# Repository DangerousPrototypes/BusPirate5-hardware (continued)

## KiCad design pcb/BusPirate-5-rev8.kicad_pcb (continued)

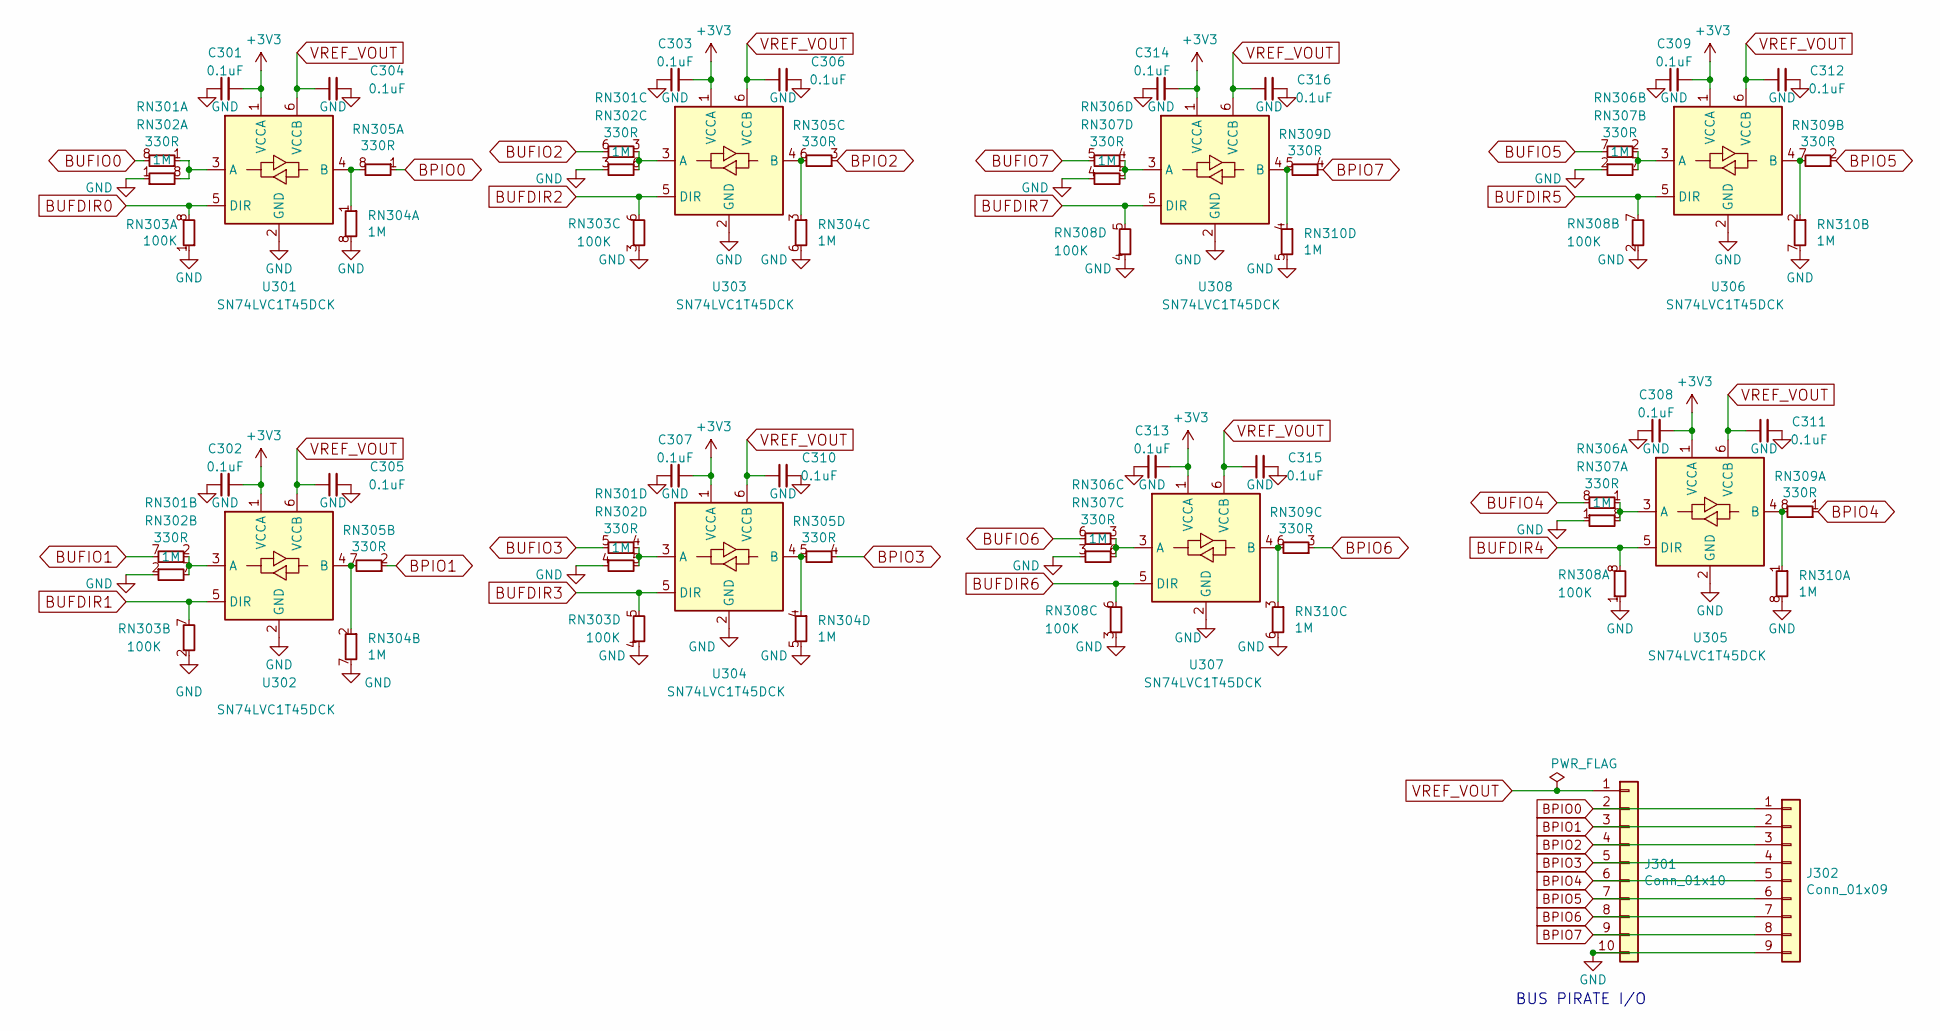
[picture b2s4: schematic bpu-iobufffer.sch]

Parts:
C301, C302, C303, C304, C305, C306, C307, C308, C309, C310, C311, C312, C313, C314, C315, C316: 0.1uF; C_0402_1005Metric
J301: Conn_01x10; PinHeader_1x10_P2.54mm_Vertical
J302: Conn_01x09; JST_SH_SM09B-SRSS-TB_1x09-1MP_P1.00mm_Horizontal
RN301, RN305, RN306, RN309: 330R; R_Array_Convex_4x0402
RN302, RN304, RN307, RN310: 1M; R_Array_Convex_4x0402
RN303, RN308: 100K; R_Array_Convex_4x0402
U301, U302, U303, U304, U305, U306, U307, U308: SN74LVC1T45DCK; SOT-363_SC-70-6

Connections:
BPIO0: J301.2, J302.1, RN305.1 (R1.1); also elsewhere on the board
BPIO1: J301.3, J302.2, RN305.2 (R1.1); also elsewhere on the board
BPIO2: J301.4, J302.3, RN305.3 (R1.1); also elsewhere on the board
BPIO3: J301.5, J302.4, RN305.4 (R1.1); also elsewhere on the board
BPIO4: J301.6, J302.5, RN309.1 (R1.1); also elsewhere on the board
BPIO5: J301.7, J302.6, RN309.2 (R1.1); also elsewhere on the board
BPIO6: J301.8, J302.7, RN309.3 (R1.1); also elsewhere on the board
BPIO7: J301.9, J302.8, RN309.4 (R1.1); also elsewhere on the board
BUFDIR0: RN303.8 (R1.8), U301.5 (DIR); also elsewhere on the board
BUFDIR1: RN303.7 (R1.8), U302.5 (DIR); also elsewhere on the board
BUFDIR2: RN303.6 (R1.8), U303.5 (DIR); also elsewhere on the board
BUFDIR3: RN303.5 (R1.8), U304.5 (DIR); also elsewhere on the board
BUFDIR4: RN308.8 (R1.8), U305.5 (DIR); also elsewhere on the board
BUFDIR5: RN308.7 (R1.8), U306.5 (DIR); also elsewhere on the board
BUFDIR6: RN308.6 (R1.8), U307.5 (DIR); also elsewhere on the board
BUFDIR7: RN308.5 (R1.8), U308.5 (DIR); also elsewhere on the board
BUFIO0: RN301.8 (R1.8); also elsewhere on the board
BUFIO1: RN301.7 (R1.8); also elsewhere on the board
BUFIO2: RN301.6 (R1.8); also elsewhere on the board
BUFIO3: RN301.5 (R1.8); also elsewhere on the board
BUFIO4: RN306.8 (R1.8); also elsewhere on the board
BUFIO5: RN306.7 (R1.8); also elsewhere on the board
BUFIO6: RN306.6 (R1.8); also elsewhere on the board
BUFIO7: RN306.5 (R1.8); also elsewhere on the board
GND: C301.1, C302.1, C303.1, C304.2, C305.2, C306.2, C307.1, C308.1, C309.1, C310.2, C311.2, C312.2, C313.1, C314.1, C315.2, C316.2, J301.10, J302.9, RN302.1 (R1.1), RN302.2 (R1.1), RN302.3 (R1.1), RN302.4 (R1.1), RN303.1 (R1.1), RN303.2 (R1.1), RN303.3 (R1.1), RN303.4 (R1.1), RN304.5 (R1.8), RN304.6 (R1.8), RN304.7 (R1.8), RN304.8 (R1.8), RN307.1 (R1.1), RN307.2 (R1.1), RN307.3 (R1.1), RN307.4 (R1.1), RN308.1 (R1.1), RN308.2 (R1.1), RN308.3 (R1.1), RN308.4 (R1.1), RN310.5 (R1.8), RN310.6 (R1.8), RN310.7 (R1.8), RN310.8 (R1.8), U301.2 (GND), U302.2 (GND), U303.2 (GND), U304.2 (GND), U305.2 (GND), U306.2 (GND), U307.2 (GND), U308.2 (GND); also elsewhere on the board
unnamed: RN301.1 (R1.1), RN302.8 (R1.8), U301.3 (A)
unnamed: RN301.2 (R1.1), RN302.7 (R1.8), U302.3 (A)
unnamed: RN301.3 (R1.1), RN302.6 (R1.8), U303.3 (A)
unnamed: RN301.4 (R1.1), RN302.5 (R1.8), U304.3 (A)
unnamed: RN304.1 (R1.1), RN305.8 (R1.8), U301.4 (B)
unnamed: RN304.2 (R1.1), RN305.7 (R1.8), U302.4 (B)
unnamed: RN304.3 (R1.1), RN305.6 (R1.8), U303.4 (B)
unnamed: RN304.4 (R1.1), RN305.5 (R1.8), U304.4 (B)
unnamed: RN306.1 (R1.1), RN307.8 (R1.8), U305.3 (A)
unnamed: RN306.2 (R1.1), RN307.7 (R1.8), U306.3 (A)
unnamed: RN306.3 (R1.1), RN307.6 (R1.8), U307.3 (A)
unnamed: RN306.4 (R1.1), RN307.5 (R1.8), U308.3 (A)
unnamed: RN309.5 (R1.8), RN310.4 (R1.1), U308.4 (B)
unnamed: RN309.6 (R1.8), RN310.3 (R1.1), U307.4 (B)
unnamed: RN309.7 (R1.8), RN310.2 (R1.1), U306.4 (B)
unnamed: RN309.8 (R1.8), RN310.1 (R1.1), U305.4 (B)
VREF_VOUT: C304.1, C305.1, C306.1, C310.1, C311.1, C312.1, C315.1, C316.1, J301.1, U301.6 (VCCB), U302.6 (VCCB), U303.6 (VCCB), U304.6 (VCCB), U305.6 (VCCB), U306.6 (VCCB), U307.6 (VCCB), U308.6 (VCCB); also elsewhere on the board

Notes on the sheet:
BUS PIRATE I/O

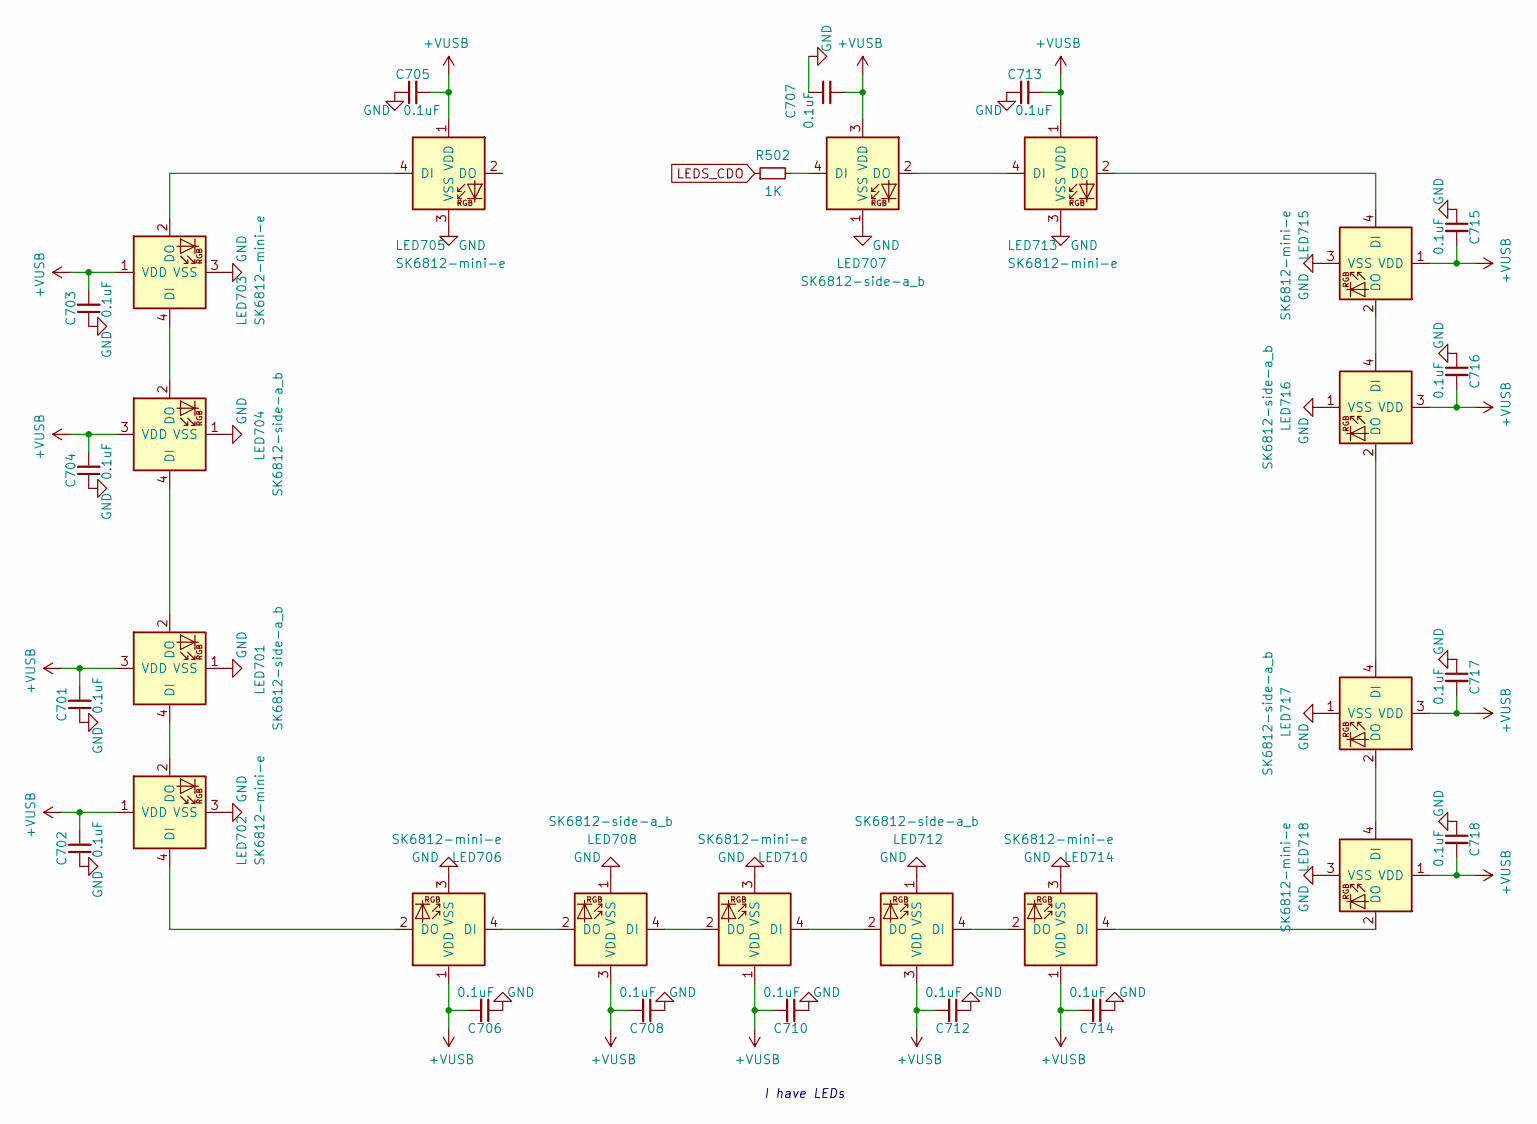
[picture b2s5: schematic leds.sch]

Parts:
C701, C702, C703, C704, C705, C706, C707, C708, C710, C712, C713, C714, C715, C716, C717, C718: 0.1uF; C_0402_1005Metric
LED701, LED704, LED707, LED708, LED712, LED716, LED717: SK6812-side-a_b
LED702, LED703, LED705, LED706, LED710, LED713, LED714, LED715, LED718: SK6812-mini-e
R502: 1K; R_0402_1005Metric

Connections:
+VUSB: C701.2, C702.2, C703.2, C704.2, C705.2, C706.2, C707.2, C708.2, C710.2, C712.2, C713.2, C714.2, C715.2, C716.2, C717.2, C718.2, LED701.3 (VDD), LED702.1 (VDD), LED703.1 (VDD), LED704.3 (VDD), LED705.1 (VDD), LED706.1 (VDD), LED707.3 (VDD), LED708.3 (VDD), LED710.1 (VDD), LED712.3 (VDD), LED713.1 (VDD), LED714.1 (VDD), LED715.1 (VDD), LED716.3 (VDD), LED717.3 (VDD), LED718.1 (VDD); also elsewhere on the board
GND: C701.1, C702.1, C703.1, C704.1, C705.1, C706.1, C707.1, C708.1, C710.1, C712.1, C713.1, C714.1, C715.1, C716.1, C717.1, C718.1, LED701.1 (VSS), LED702.3 (VSS), LED703.3 (VSS), LED704.1 (VSS), LED705.3 (VSS), LED706.3 (VSS), LED707.1 (VSS), LED708.1 (VSS), LED710.3 (VSS), LED712.1 (VSS), LED713.3 (VSS), LED714.3 (VSS), LED715.3 (VSS), LED716.1 (VSS), LED717.1 (VSS), LED718.3 (VSS); also elsewhere on the board
LEDS_CDO: R502.1; also elsewhere on the board
unnamed: LED701.2 (DO), LED704.4 (DI)
unnamed: LED701.4 (DI), LED702.2 (DO)
unnamed: LED702.4 (DI), LED706.2 (DO)
unnamed: LED703.2 (DO), LED705.4 (DI)
unnamed: LED703.4 (DI), LED704.2 (DO)
unnamed: LED706.4 (DI), LED708.2 (DO)
unnamed: LED707.2 (DO), LED713.4 (DI)
unnamed: LED707.4 (DI), R502.2
unnamed: LED708.4 (DI), LED710.2 (DO)
unnamed: LED710.4 (DI), LED712.2 (DO)
unnamed: LED712.4 (DI), LED714.2 (DO)
unnamed: LED713.2 (DO), LED715.4 (DI)
unnamed: LED714.4 (DI), LED718.2 (DO)
unnamed: LED715.2 (DO), LED716.4 (DI)
unnamed: LED716.2 (DO), LED717.4 (DI)
unnamed: LED717.2 (DO), LED718.4 (DI)

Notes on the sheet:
I have LEDs

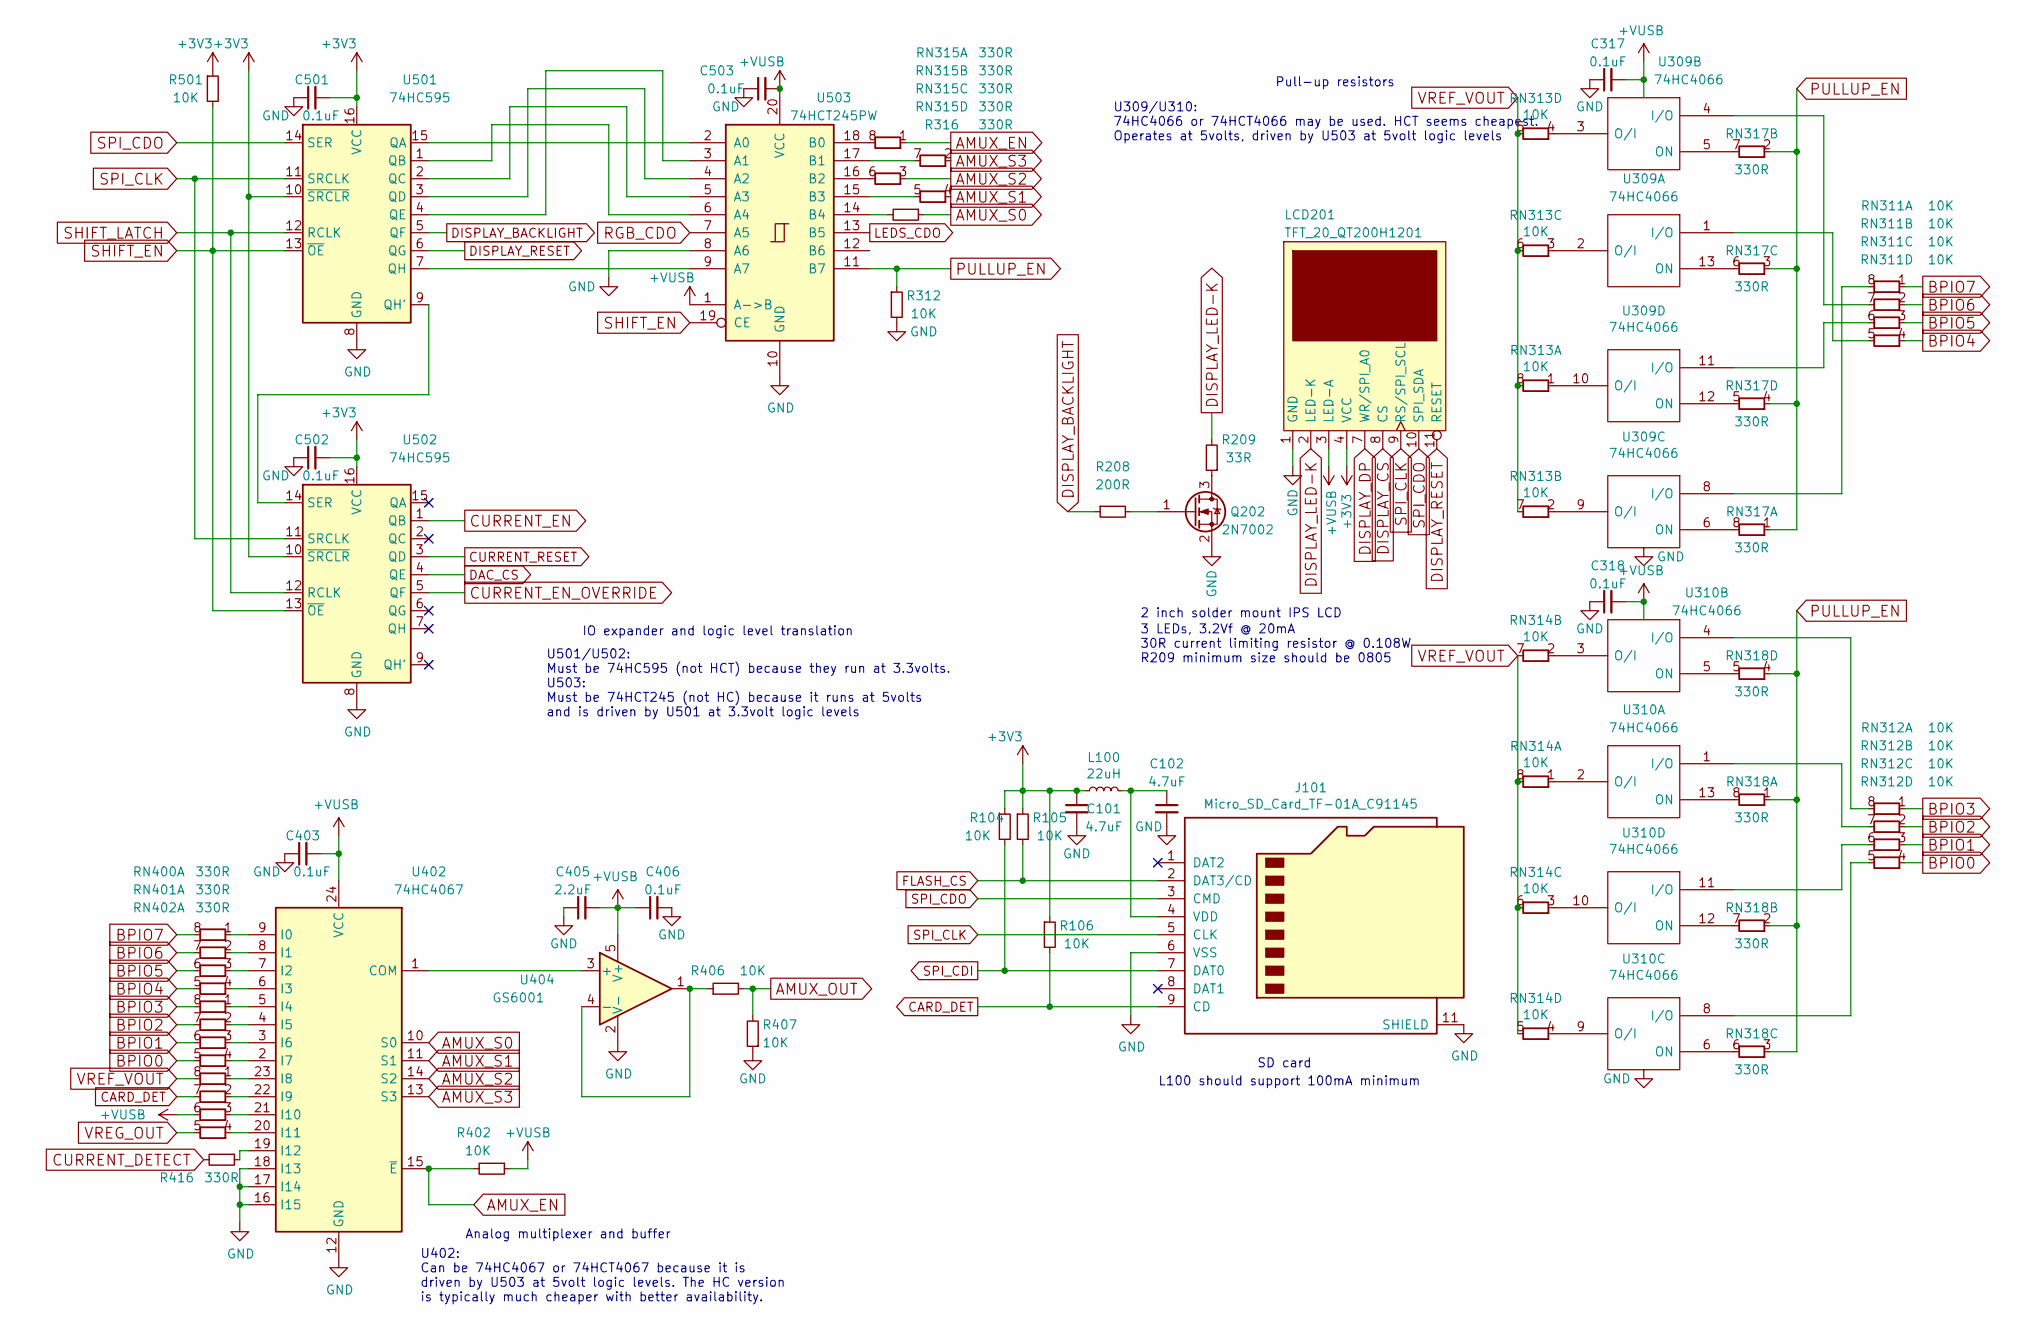
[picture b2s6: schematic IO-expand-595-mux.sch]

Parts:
C101, C102: 4.7uF; C_0402_1005Metric
C317, C318, C403, C406, C501, C502, C503: 0.1uF; C_0402_1005Metric
C405: 2.2uF; C_0402_1005Metric
J101: Micro_SD_Card_TF-01A_C91145; TF-01A_C91145
L100: 22uH; L_0603_1608Metric
LCD201: TFT_20_QT200H1201
Q202: 2N7002; SOT-23
R104, R105, R106, R312, R402, R406, R407, R501: 10K; R_0402_1005Metric
R208: 200R; R_0402_1005Metric
R209: 33R; R_0805_2012Metric
R316, R416: 330R; R_0402_1005Metric
RN311, RN312, RN313, RN314: 10K; R_Array_Convex_4x0402
RN315, RN317, RN318, RN400, RN401, RN402: 330R; R_Array_Convex_4x0402
U309, U310: 74HC4066; TSSOP-14_4.4x5mm_P0.65mm
U402: 74HC4067; TSSOP-24_4.4x7.8mm_P0.65mm
U404: GS6001; SOT-23-5
U501, U502: 74HC595; TSSOP-16_4.4x5mm_P0.65mm
U503: 74HCT245PW; TSSOP-20_4.4x6.5mm_P0.65mm

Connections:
+VUSB: C317.2, C318.2, C403.2, C405.2, C406.1, C503.2, LCD201.3 (LED-A), R402.1, RN402.6 (R1.8), U309.14 (Vdd), U310.14 (Vdd), U402.24 (VCC), U404.5 (V+), U503.1 (A->B), U503.20 (VCC); also elsewhere on the board
AMUX_EN: R402.2, RN315.1 (R1.1), U402.15 (~E)
AMUX_OUT: R406.2, R407.2; also elsewhere on the board
AMUX_S0: R316.1, U402.10 (S0)
AMUX_S1: RN315.4 (R1.1), U402.11 (S1)
AMUX_S2: RN315.3 (R1.1), U402.14 (S2)
AMUX_S3: RN315.2 (R1.1), U402.13 (S3)
BPIO0: RN312.4 (R1.1), RN401.5 (R1.8); also elsewhere on the board
BPIO1: RN312.3 (R1.1), RN401.6 (R1.8); also elsewhere on the board
BPIO2: RN312.2 (R1.1), RN401.7 (R1.8); also elsewhere on the board
BPIO3: RN312.1 (R1.1), RN401.8 (R1.8); also elsewhere on the board
BPIO4: RN311.4 (R1.1), RN400.5 (R1.8); also elsewhere on the board
BPIO5: RN311.3 (R1.1), RN400.6 (R1.8); also elsewhere on the board
BPIO6: RN311.2 (R1.1), RN400.7 (R1.8); also elsewhere on the board
BPIO7: RN311.1 (R1.1), RN400.8 (R1.8); also elsewhere on the board
CARD_DET: J101.9 (CD), R106.2, RN402.7 (R1.8)
CURRENT_DETECT: R416.2; also elsewhere on the board
CURRENT_EN: U502.1 (QB); also elsewhere on the board
CURRENT_EN_OVERRIDE: U502.5 (QF); also elsewhere on the board
CURRENT_RESET: U502.3 (QD); also elsewhere on the board
DAC_CS: U502.4 (QE)
DISPLAY_BACKLIGHT: R208.1, U501.5 (QF)
DISPLAY_CS: LCD201.8 (CS); also elsewhere on the board
DISPLAY_DP: LCD201.7 (WR/SPI_A0); also elsewhere on the board
DISPLAY_LED-K: LCD201.2 (LED-K), R209.2
DISPLAY_RESET: LCD201.11 (RESET), U501.6 (QG)
FLASH_CS: J101.2 (DAT3/CD), R105.2; also elsewhere on the board
GND: C101.2, C102.2, C317.1, C318.1, C403.1, C405.1, C406.2, C501.1, C502.1, C503.1, J101.6 (VSS), J101.11 (SHIELD), LCD201.1 (GND), LCD201.5 (GND), LCD201.6 (GND), LCD201.12 (GND), Q202.2 (S), R312.2, R407.1, U309.7 (Vss), U310.7 (Vss), U402.12 (GND), U402.16 (I15), U402.17 (I14), U402.18 (I13), U404.2 (V-), U501.8 (GND), U502.8 (GND), U503.8 (A6), U503.10 (GND); also elsewhere on the board
LEDS_CDO: U503.13 (B5); also elsewhere on the board
unnamed: C102.1, J101.4 (VDD), L100.2
unnamed: Q202.1 (G), R208.2
unnamed: Q202.3 (D), R209.1
unnamed: R316.2, U503.14 (B4)
unnamed: R406.1, U404.1, U404.4 (-)
unnamed: R416.1, U402.19 (I12)
unnamed: RN311.5 (R1.8), U309.1 (I/O)
unnamed: RN311.6 (R1.8), U309.11 (I/O)
unnamed: RN311.7 (R1.8), U309.4 (I/O)
unnamed: RN311.8 (R1.8), U309.8 (I/O)
unnamed: RN312.5 (R1.8), U310.8 (I/O)
unnamed: RN312.6 (R1.8), U310.11 (I/O)
unnamed: RN312.7 (R1.8), U310.1 (I/O)
unnamed: RN312.8 (R1.8), U310.4 (I/O)
unnamed: RN313.1 (R1.1), U309.10 (O/I)
unnamed: RN313.2 (R1.1), U309.9 (O/I)
unnamed: RN313.3 (R1.1), U309.2 (O/I)
unnamed: RN313.4 (R1.1), U309.3 (O/I)
unnamed: RN314.1 (R1.1), U310.2 (O/I)
unnamed: RN314.2 (R1.1), U310.3 (O/I)
unnamed: RN314.3 (R1.1), U310.10 (O/I)
unnamed: RN314.4 (R1.1), U310.9 (O/I)
unnamed: RN315.5 (R1.8), U503.15 (B3)
unnamed: RN315.6 (R1.8), U503.16 (B2)
unnamed: RN315.7 (R1.8), U503.17 (B1)
unnamed: RN315.8 (R1.8), U503.18 (B0)
unnamed: RN317.5 (R1.8), U309.12 (ON)
unnamed: RN317.6 (R1.8), U309.13 (ON)
unnamed: RN317.7 (R1.8), U309.5 (ON)
unnamed: RN317.8 (R1.8), U309.6 (ON)
unnamed: RN318.5 (R1.8), U310.5 (ON)
unnamed: RN318.6 (R1.8), U310.6 (ON)
unnamed: RN318.7 (R1.8), U310.12 (ON)
unnamed: RN318.8 (R1.8), U310.13 (ON)
unnamed: RN400.1 (R1.1), U402.9 (I0)
unnamed: RN400.2 (R1.1), U402.8 (I1)
unnamed: RN400.3 (R1.1), U402.7 (I2)
unnamed: RN400.4 (R1.1), U402.6 (I3)
unnamed: RN401.1 (R1.1), U402.5 (I4)
unnamed: RN401.2 (R1.1), U402.4 (I5)
unnamed: RN401.3 (R1.1), U402.3 (I6)
unnamed: RN401.4 (R1.1), U402.2 (I7)
unnamed: RN402.1 (R1.1), U402.23 (I8)
unnamed: RN402.2 (R1.1), U402.22 (I9)
unnamed: RN402.3 (R1.1), U402.21 (I10)
unnamed: RN402.4 (R1.1), U402.20 (I11)
unnamed: U402.1 (COM), U404.3 (+)
unnamed: U501.1 (QB), U503.6 (A4)
unnamed: U501.2 (QC), U503.5 (A3)
unnamed: U501.3 (QD), U503.4 (A2)
unnamed: U501.4 (QE), U503.3 (A1)
unnamed: U501.7 (QH), U503.9 (A7)
unnamed: U501.9 (QH'), U502.14 (SER)
unnamed: U501.15 (QA), U503.2 (A0)
PULLUP_EN: R312.1, RN317.1 (R1.1), RN317.2 (R1.1), RN317.3 (R1.1), RN317.4 (R1.1), RN318.1 (R1.1), RN318.2 (R1.1), RN318.3 (R1.1), RN318.4 (R1.1), U503.11 (B7)
RGB_CDO: U503.7 (A5); also elsewhere on the board
SHIFT_EN: R501.2, U501.13 (~OE), U502.13 (~OE), U503.19 (CE); also elsewhere on the board
SHIFT_LATCH: U501.12 (RCLK), U502.12 (RCLK); also elsewhere on the board
SPI_CDI: J101.7 (DAT0), R104.2; also elsewhere on the board
SPI_CDO: J101.3 (CMD), LCD201.10 (SPI_SDA), U501.14 (SER); also elsewhere on the board
SPI_CLK: J101.5 (CLK), LCD201.9 (RS/SPI_SCL), U501.11 (SRCLK), U502.11 (SRCLK); also elsewhere on the board
VREF_VOUT: RN313.5 (R1.8), RN313.6 (R1.8), RN313.7 (R1.8), RN313.8 (R1.8), RN314.5 (R1.8), RN314.6 (R1.8), RN314.7 (R1.8), RN314.8 (R1.8), RN402.8 (R1.8); also elsewhere on the board
VREG_OUT: RN402.5 (R1.8); also elsewhere on the board

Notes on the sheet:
IO expander and logic level translation
U501/U502: Must be 74HC595 (not HCT) because they run at 3.3volts. U503: Must be 74HCT245 (not HC) because it runs at 5volts and is driven by U501 at 3.3volt logic levels
Analog multiplexer and buffer
U402: Can be 74HC4067 or 74HCT4067 because it is driven by U503 at 5volt logic levels. The HC version is typically much cheaper with better availability.
SD card
2 inch solder mount IPS LCD
3 LEDs, 3.2Vf @ 20mA 30R current limiting resistor @ 0.108W R209 minimum size should be 0805
L100 should support 100mA minimum
Pull-up resistors
U309/U310: 74HC4066 or 74HCT4066 may be used. HCT seems cheapest. Operates at 5volts, driven by U503 at 5volt logic levels

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
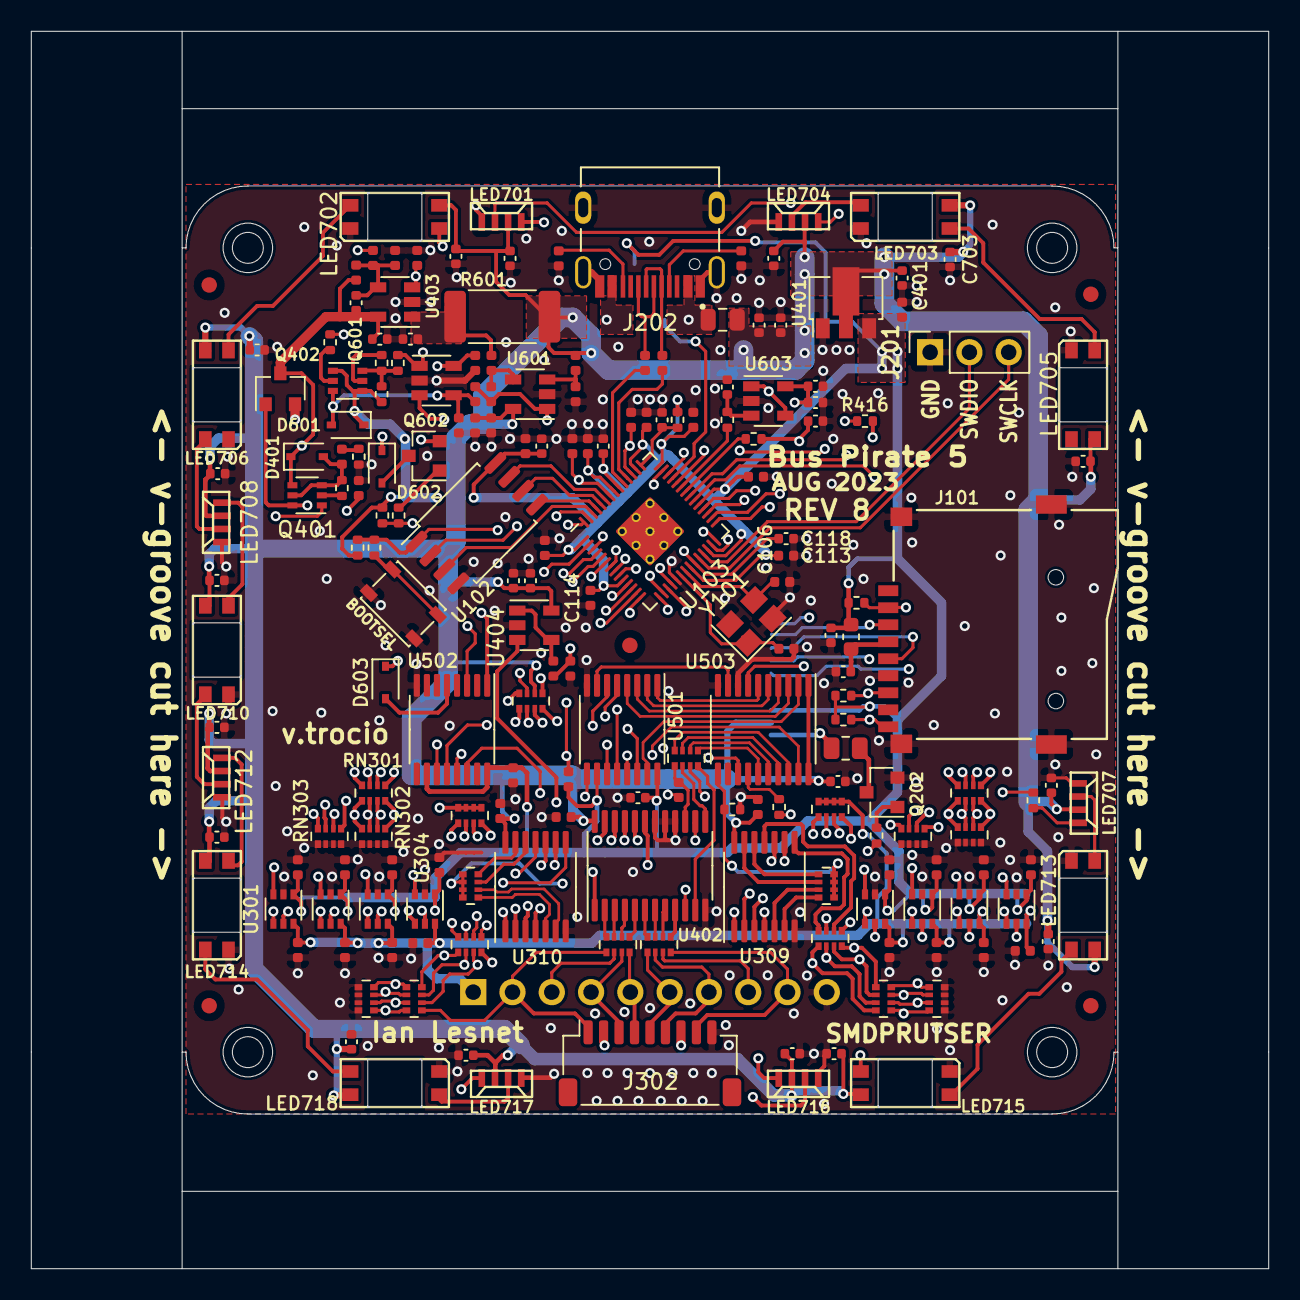
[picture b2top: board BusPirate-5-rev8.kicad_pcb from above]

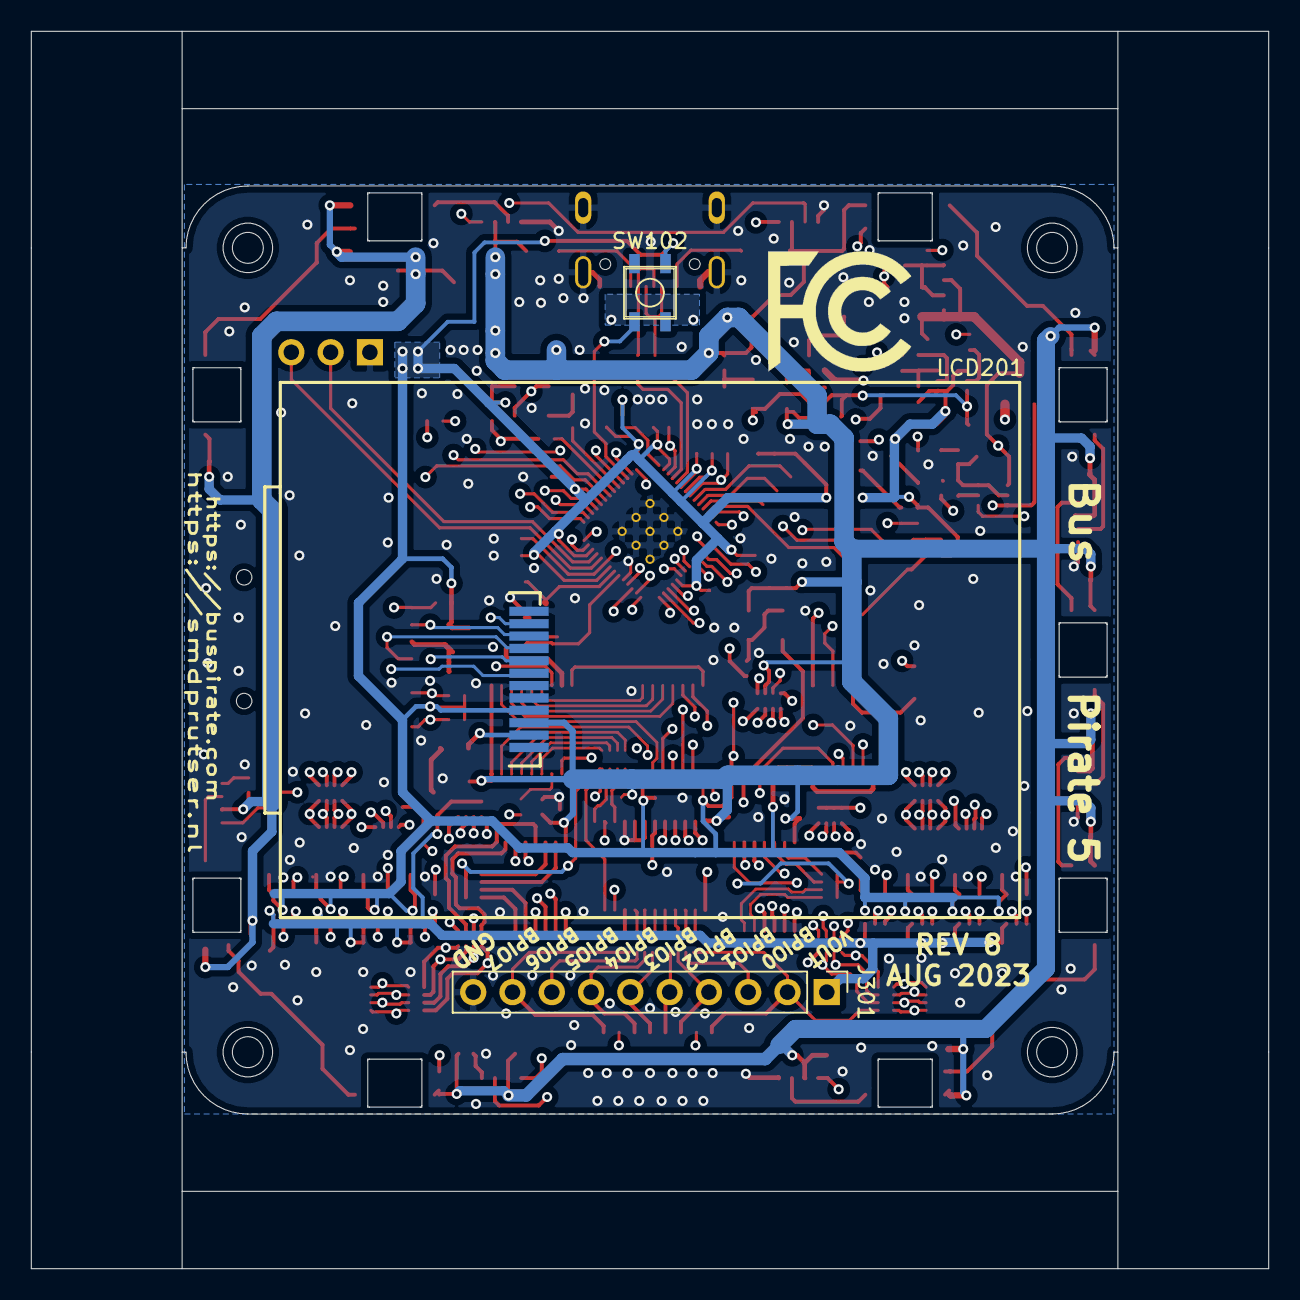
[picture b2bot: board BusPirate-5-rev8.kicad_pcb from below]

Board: 4 copper layers, 80.0 x 80.0 mm, 203 parts (4 on the bottom side), 182 nets.

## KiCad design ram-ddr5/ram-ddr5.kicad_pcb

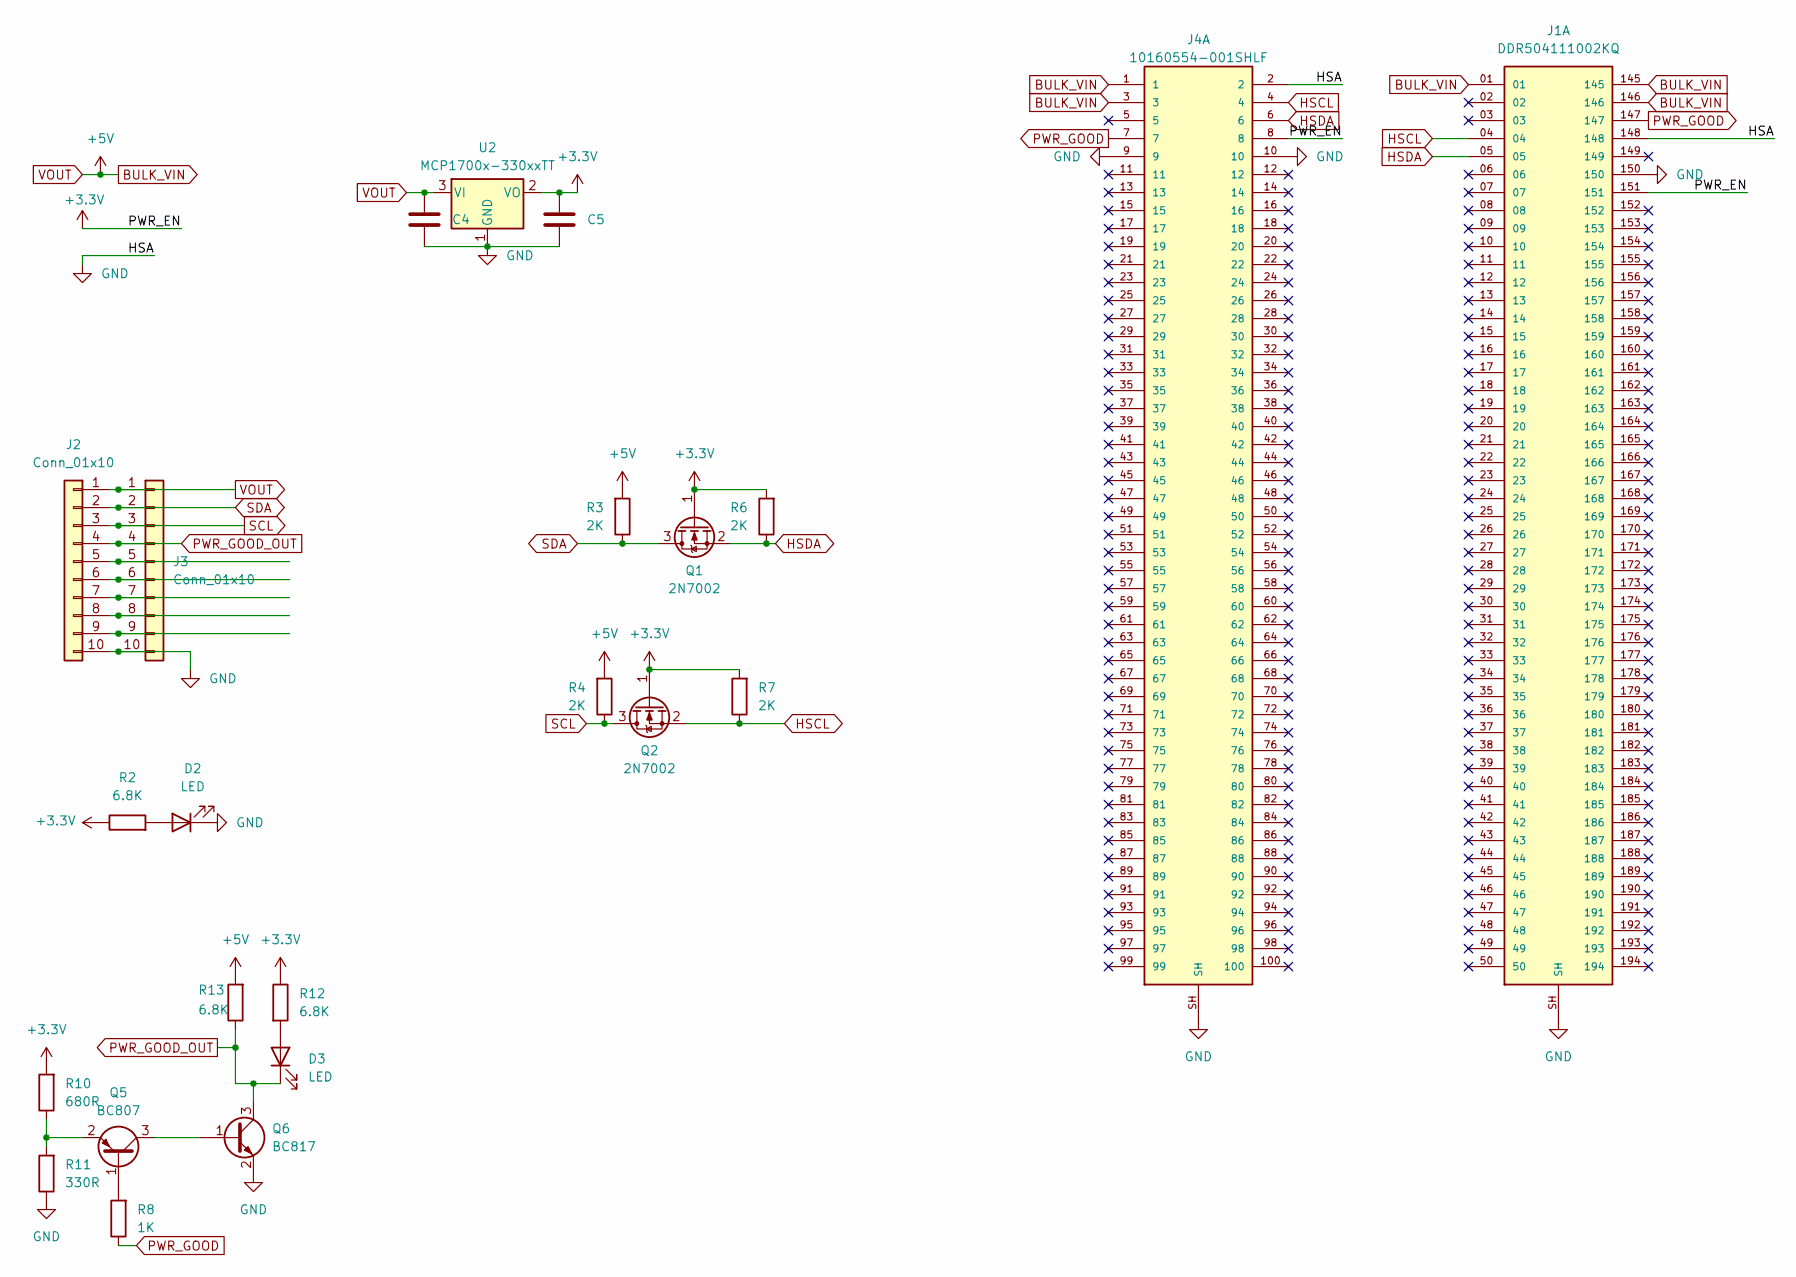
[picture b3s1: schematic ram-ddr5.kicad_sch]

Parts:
C4, C5: 10uF/6.3V; C_0805_2012Metric
D2, D3: LED; LED_0805_2012Metric
J1: DDR504111002KQ; AMPHENOL_DDR504111002KQ; PARTREV 10
J2: Conn_01x10; PinSocket_1x10_P2.54mm_Horizontal
J3: Conn_01x10; PinHeader_1x10_P2.54mm_Vertical
J4: 10160554-001SHLF; AMPHENOL_10160554-001SHLF; PARTREV A
Q1, Q2: 2N7002; SOT-23
Q5: BC807; SOT-23
Q6: BC817; SOT-23
R2, R12, R13: 6.8K; R_0805_2012Metric
R3, R4, R6, R7: 2K; R_0805_2012Metric
R8: 1K; R_0805_2012Metric
R10: 680R; R_0805_2012Metric
R11: 330R; R_0805_2012Metric
U2: MCP1700x-330xxTT; SOT-23

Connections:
+3.3V: C5.1, J1.151, J4.8, Q1.1 (G), Q2.1 (G), R2.1, R6.2, R7.2, R10.2, R12.1, U2.2 (VO)
BULK_VIN: C4.1, J1.01, J1.145, J1.146, J2.1, J3.1, J4.1, J4.3, R3.2, R4.2, R13.2, U2.3 (VI)
GND: C4.2, C5.2, D2.1 (K), J1.148, J1.150, J1.SH, J2.10, J3.10, J4.2, J4.9, J4.10, J4.SH, Q6.2 (E), R11.1, U2.1 (GND)
HSCL: J1.04, J4.4, Q2.2 (S), R7.1
HSDA: J1.05, J4.6, Q1.2 (S), R6.1
unnamed: D2.2 (A), R2.2
unnamed: D3.2 (A), R12.2
unnamed: J2.5, J3.5
unnamed: J2.6, J3.6
unnamed: J2.7, J3.7
unnamed: J2.8, J3.8
unnamed: J2.9, J3.9
unnamed: Q5.1 (B), R8.2
unnamed: Q5.3 (C), Q6.1 (B)
unnamed: Q5.2 (E), R10.1, R11.2
PWR_GOOD: J1.147, J4.7, R8.1
PWR_GOOD_OUT: D3.1 (K), J2.4, J3.4, Q6.3 (C), R13.1
SCL: J2.3, J3.3, Q2.3 (D), R4.1
SDA: J2.2, J3.2, Q1.3 (D), R3.1

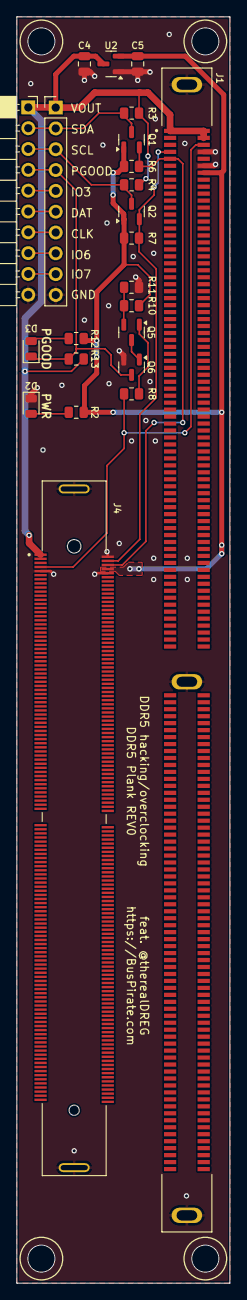
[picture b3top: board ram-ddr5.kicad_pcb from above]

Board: 2 copper layers, 26.0 x 154.5 mm, 23 parts (0 on the bottom side), 19 nets.
